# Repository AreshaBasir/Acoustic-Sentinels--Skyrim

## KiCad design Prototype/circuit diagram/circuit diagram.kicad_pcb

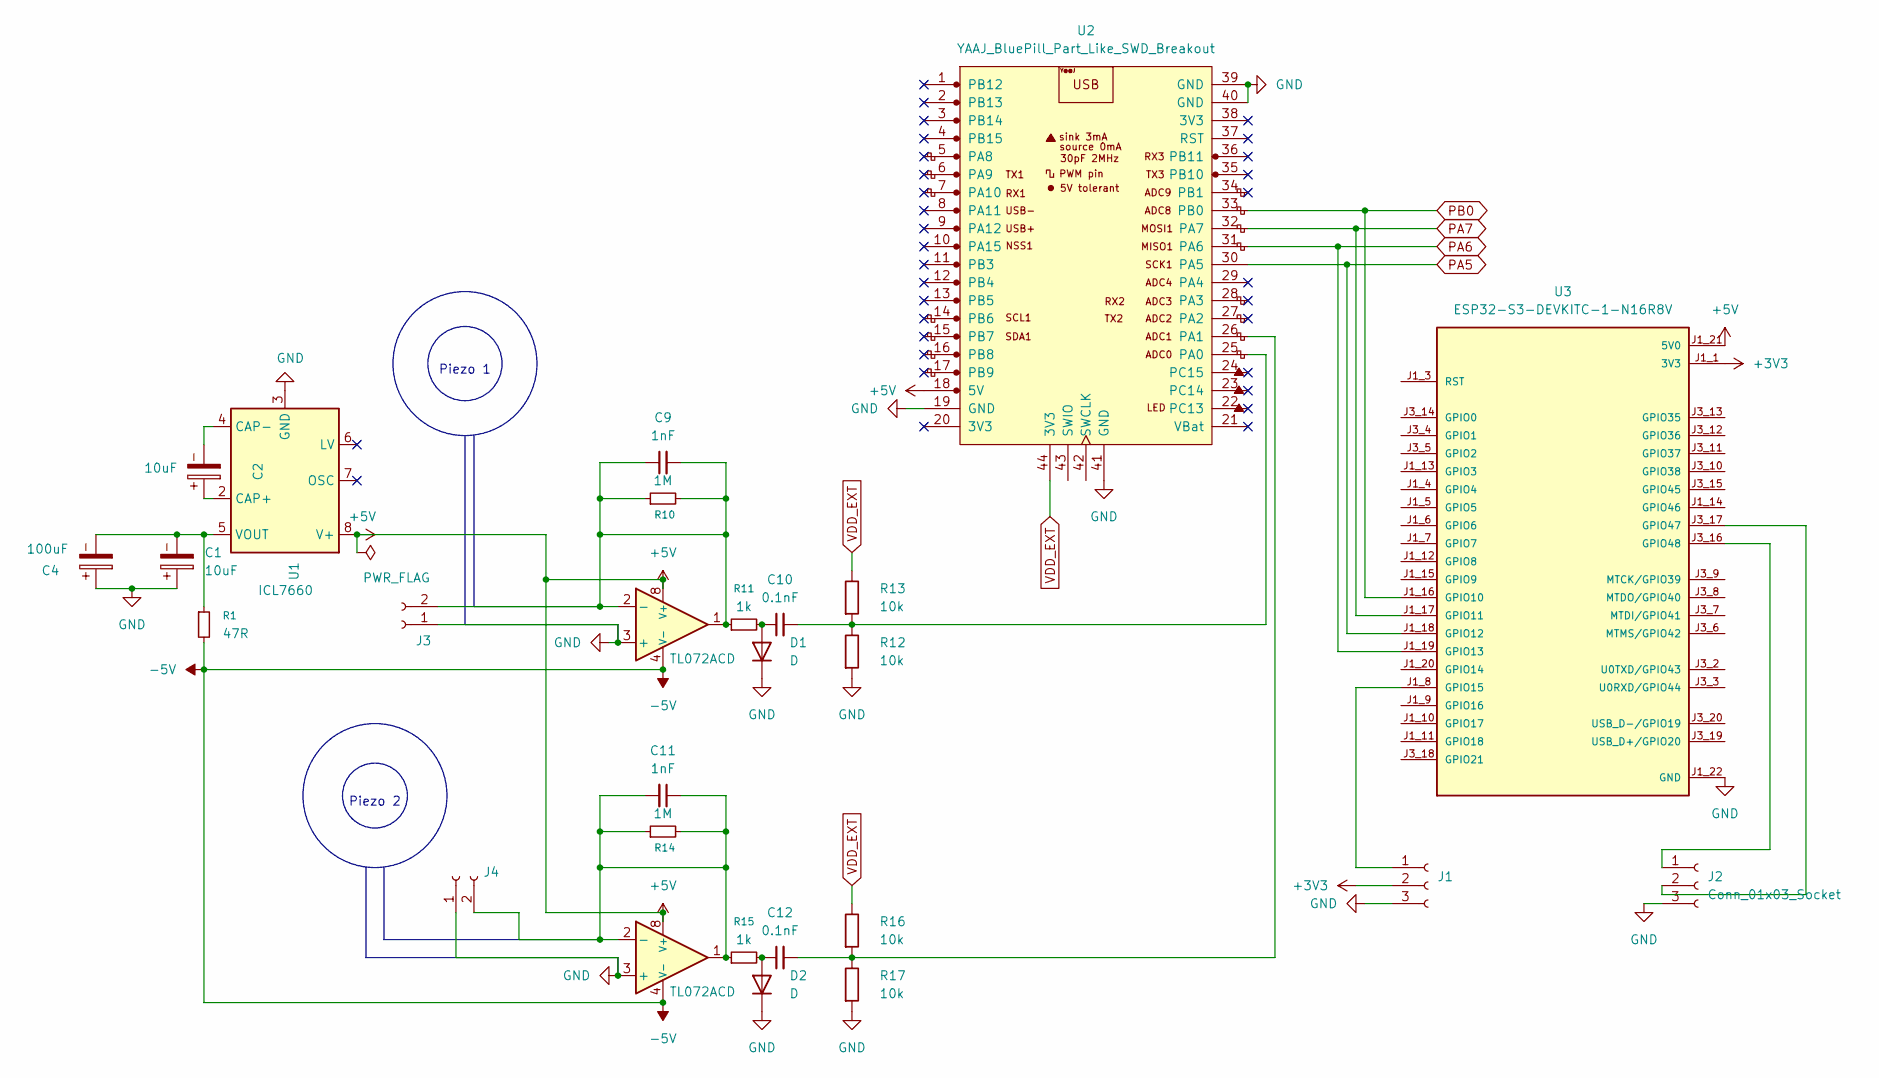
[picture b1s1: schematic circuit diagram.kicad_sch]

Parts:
C1: 10uF; CP_Radial_D4.0mm_P1.50mm
C2: 10uF; CP_Radial_D5.0mm_P2.00mm
C4: 100uF; CP_Radial_D8.0mm_P3.50mm
C9, C11: 1nF; C_Disc_D10.5mm_W5.0mm_P5.00mm
C10: 0.1nF; C_Disc_D7.5mm_W2.5mm_P5.00mm
C12: 0.1nF; C_Disc_D10.5mm_W5.0mm_P5.00mm
D1, D2: D; D_5KPW_P7.62mm_Vertical_AnodeUp
J1, J2: Conn_01x03_Socket; Hirose_DF63M-3P-3.96DSA_1x03_P3.96mm_Vertical
J3, J4: Conn_01x02_Socket; JST_PH_B2B-PH-K_1x02_P2.00mm_Vertical
R1: 47R; R_Axial_DIN0204_L3.6mm_D1.6mm_P7.62mm_Horizontal
R10, R14: 1M; R_Axial_DIN0204_L3.6mm_D1.6mm_P7.62mm_Horizontal
R11, R15: 1k; R_Axial_DIN0204_L3.6mm_D1.6mm_P7.62mm_Horizontal
R12, R13, R16, R17: 10k; R_Axial_DIN0207_L6.3mm_D2.5mm_P10.16mm_Horizontal
U1: ICL7660; SO08
U2: YAAJ_BluePill_Part_Like_SWD_Breakout; YAAJ_BluePill_SWD_1
U3: ESP32-S3-DEVKITC-1-N16R8V; XCVR_ESP32-S3-DEVKITC-1-N16R8V; PARTREV 1.1
U6, U7: TL072ACD; DIP794W45P254L1060H508Q8

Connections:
+3V3: J1.2, U3.J1_1 (3V3), U3.J1_2 (3V3)
+5V: U1.8 (V+), U2.18 (5V), U3.J1_21 (5V0), U6.8 (V+), U7.8 (V+)
-5V: R1.2, U6.4 (V-), U7.4 (V-)
GND: C1.1, C4.1, D1.1 (K), D2.1 (K), J1.3, J2.3, J3.1, J4.1, R12.1, R17.1, U1.3 (GND), U2.19 (GND), U2.39 (GND), U2.40 (GND), U2.41 (GND), U3.J1_22 (GND), U3.J3_1 (GND), U3.J3_21 (GND), U3.J3_22 (GND), U6.3 (+), U7.3 (+)
unnamed: C10.1, D1.2 (A), R11.2
unnamed: C12.1, D2.2 (A), R15.2
unnamed: J1.1, U3.J1_8 (GPIO15)
unnamed: J2.1, U3.J3_16 (GPIO48)
unnamed: J2.2, U3.J3_17 (GPIO47)
unnamed: C11.1, C11.2, J4.2, R14.1, R14.2, R15.1, U7.1, U7.2 (-)
unnamed: C2.1, U1.2 (CAP+)
unnamed: C2.2, U1.4 (CAP-)
unnamed: C1.2, C4.2, R1.1, U1.5 (VOUT)
unnamed: C10.2, R12.2, R13.1, U2.25 (PA0)
unnamed: C12.2, R16.1, R17.2, U2.26 (PA1)
PA5: U2.30 (PA5), U3.J1_18 (GPIO12)
PA6: U2.31 (PA6), U3.J1_19 (GPIO13)
PA7: U2.32 (PA7), U3.J1_17 (GPIO11)
PB0: U2.33 (PB0), U3.J1_16 (GPIO10)
VDD_EXT: R13.2, R16.2, U2.44 (3V3)

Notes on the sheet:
Piezo 2
Piezo 1

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
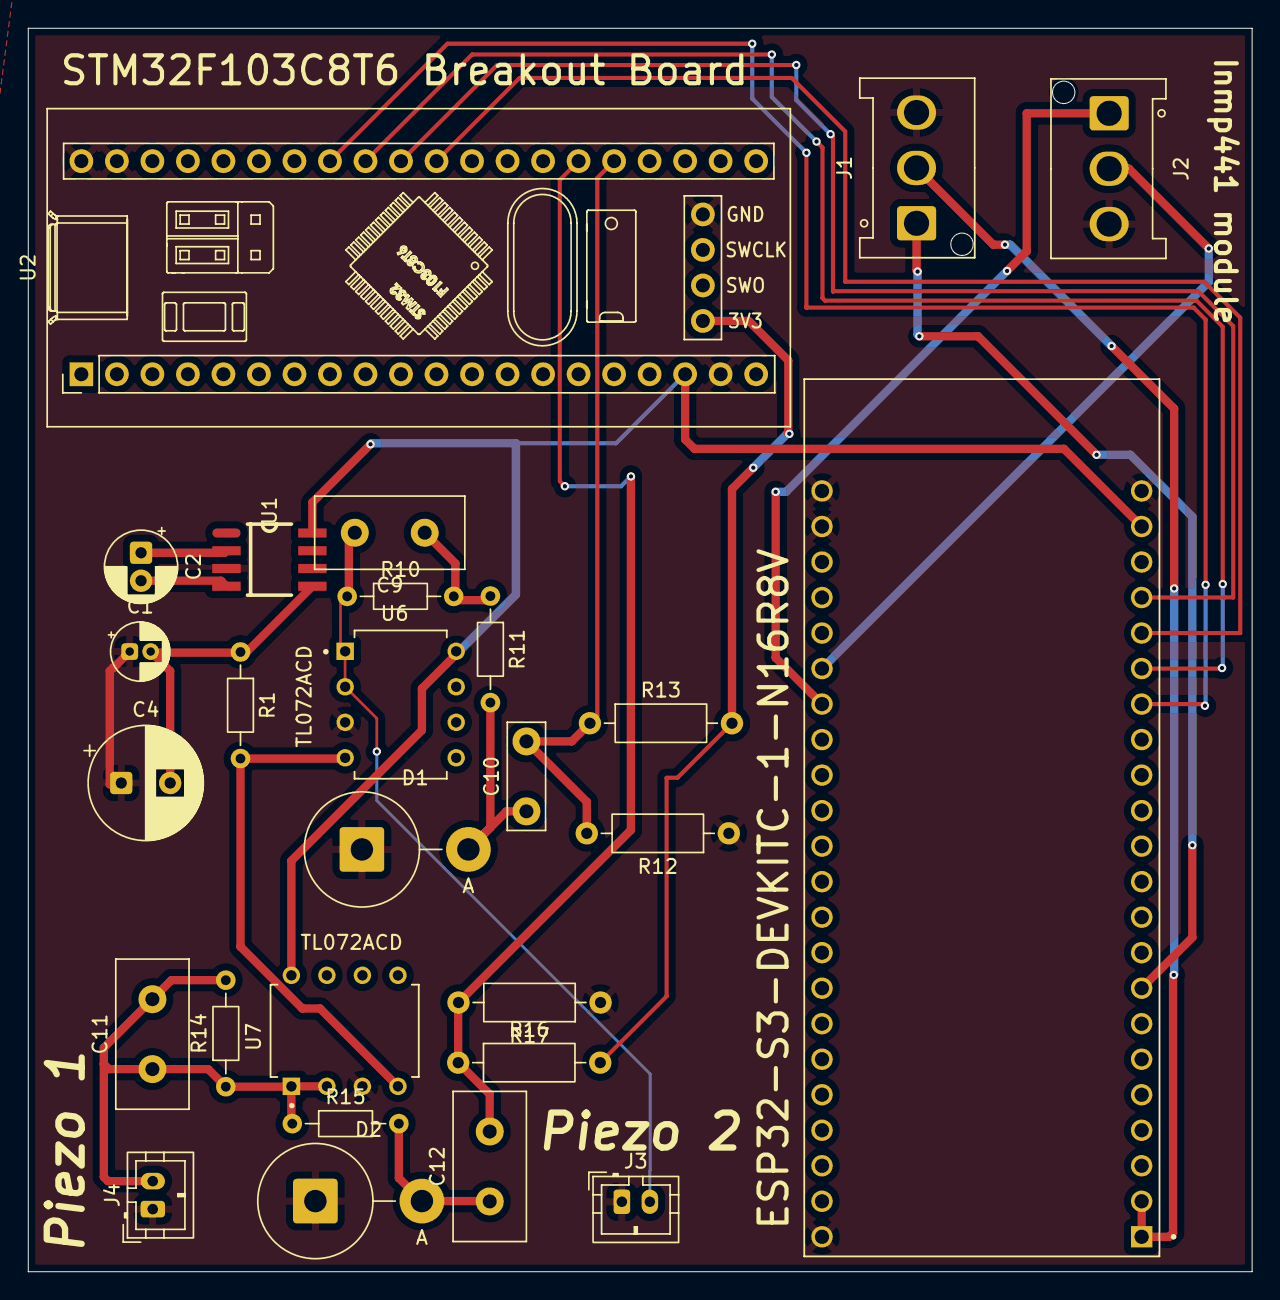
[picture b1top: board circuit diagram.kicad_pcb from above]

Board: 2 copper layers, 87.5 x 88.9 mm, 27 parts (0 on the bottom side), 22 nets.

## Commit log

2026-05-23 Initial commit: Airbus Fly your ideas all files
2026-05-24 refactor: update dataset nomenclature to use professional bare motor terminology
2026-05-24 updated the code with improved performance metrices and logic for optimized multi dimentional detection
